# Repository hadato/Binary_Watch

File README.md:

# Binary Watch

This is a project of binary watch which is able to show time, date and its battery level. Three side LEDs show what is currently on display. The watch is based on an ATMega328p and a PCF8563 real-time clock. All control is done using one press bottom. Light-sensing is implemented for brightness adjustments. 

## Description

### Repository and Project Status

The repository contains a first prototype of the watch to be implemented in a wooden hand watch. Both source code, board design files are included. The first prototype has been implemented on a breadboard and is fully functional. The second prototype was build in a wooden wrist watch and is fully functional.

### Main Watch Components
- 25 LEDs
- ATMega328p microcontroller
- PCF8563 real-time clock
- Small tactile switch
- MCP73831T Li-Ion battery charger
- Rechargeable 2032 Li-Ion battery
- Phototransistor for LED intensity adjustment
- USB connector for charging

### Working Principle

The main part of the project is based on an 8-bit microcontroller (uC) ATMega328p connected to the PCF8563 real-time clock (RTC) using I2C. The RTC keeps the correct time, whereas the uC is responsible for all logical operations, inputs from the button and LED output. When the button is pressed, the uC wakes up and the current time is read from the RTC. The time (hours, minutes, seconds) is displayed in a binary-coded decimal (BCD) format on the LEDs using multiplexing. If the button is pressed shortly once more, date (day, month, year) is displayed. Third short press shows the battery voltage. Another short press puts the uC to the sleep mode again. If the button is not pressed for more than 8 s, the uC goes to the sleep mode and all LED are turned off. If a longer press is performed, the watch goes into the sleep mode from either of the previous states. 

To enter the time-setting mode, the button has to be pressed for more than 1 s in either of the previously mentioned modes. If the time-setting mode is entered, a variable to be set starts to blink (first, variable second starts to blink). A short press increments the corresponding variable, longer press (over 0.25s) moves to the next variable (seconds -> minutes -> hours -> day -> month -> year), extra long press confirms the changes and makes the watch to return to the time-display mode.

To save the energy during the run-time and minimize the parts-count, the uC runs on an internal 1 MHz oscillator.

### Code

Note: As included, the code is working though it is still under development and far from being optimal.

The watch is programmed in C++ and is split into three different parts. For the communication with the RTC, twi.h and twi.cpp files were created. For the basic watch operation (button press, LED multiplexing, time reading/setting) a watch.h and watch.cpp files were created. The main.cpp then binds everything together. 

### Board Design

The board is designe using EAGLE and its lates version (9.5.1). The file Top_final shows a look of the watch, the files Top_copper and Bot_copper show the board design. Files BinaryWatch_v0_4_OptR_fix are the EAGLE files.

## Future Goals

- Improve the coding and commenting
- Making a more versatile design which can be used in different watches ranging from tiny hand watches to table/wall watches.
- Implement USB communication with PC to be able to conveniently set up time on the watch (different uC needed).

## Other Pictures

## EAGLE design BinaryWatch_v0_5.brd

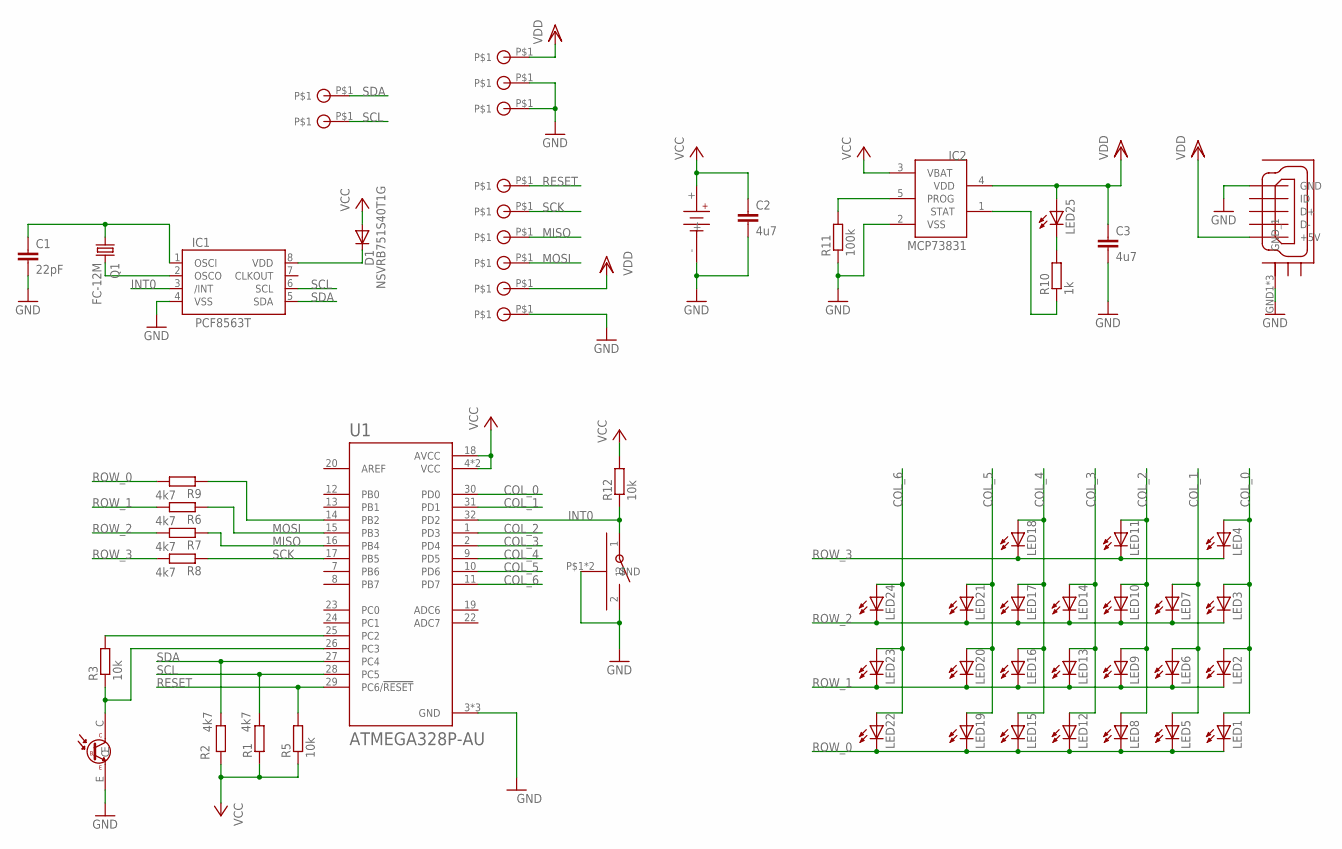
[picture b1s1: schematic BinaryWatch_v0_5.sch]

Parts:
C1: 22pF; C0603
C2, C3: 4u7; C0603
D1: NSVRB751S40T1G; SOD523
IC1: PCF8563T; SO8
IC2: MCP73831; SOT23-5L
LED1, LED2, LED3, LED4, LED5, LED6, LED7, LED8, LED9, LED10, LED11, LED12, LED13, LED14, LED15, LED16, LED17, LED18, LED19, LED20, LED21, LED22, LED23, LED24, LED25: LEDSML0603; SML0603
Q1: FC-12M
R1, R2, R6, R7, R8, R9: 4k7; R0603
R3, R5, R12: 10k; R0603
R10: 1k; R0603
R11: 100k; R0603
U1: ATMEGA328P-AU; QFP80P900X900X120-32N
U$1: 2032; 2032_45DEG
U$2, U$3, U$4, U$5, U$6, U$7, U$9, U$11, U$12, U$13, U$14: CONTACT_1_8MM
U$8: TACK_SWITCH; TL3330
U$10: MICRO_USB_VERTICAL
U$15: PHOTOTRANSISTOR_0603; PHOTO_TRANS_0603

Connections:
COL_0: LED1.A, LED2.A, LED3.A, LED4.A, U1.30 (PD0)
COL_1: LED5.A, LED6.A, LED7.A, U1.31 (PD1)
COL_2: LED8.A, LED9.A, LED10.A, LED11.A, U1.1 (PD3)
COL_3: LED12.A, LED13.A, LED14.A, U1.2 (PD4)
COL_4: LED15.A, LED16.A, LED17.A, LED18.A, U1.9 (PD5)
COL_5: LED19.A, LED20.A, LED21.A, U1.10 (PD6)
COL_6: LED22.A, LED23.A, LED24.A, U1.11 (PD7)
GND: C1.2, C2.2, C3.2, IC1.4 (VSS), IC2.2 (VSS), R11.1, U1.3 (GND), U1.5 (GND), U1.21 (GND), U$1.-, U$2.P$1, U$8.2, U$8.P$1 (GND), U$8.P$2 (GND), U$9.P$1, U$10.5 (GND), U$10.GND1 (GND_1), U$10.GND2 (GND_1), U$10.GND3 (GND_1), U$12.P$1, U$15.E
INT0: IC1.3 (/INT), R12.1, U1.32 (PD2), U$8.1
MISO: R7.1, U1.16 (PB4), U$5.P$1
MOSI: R6.1, U1.15 (PB3), U$4.P$1
unnamed: IC1.2 (OSCO), Q1.2
unnamed: C1.1, IC1.1 (OSCI), Q1.1
unnamed: R3.1, U1.26 (PC3), U$15.C
unnamed: R3.2, U1.25 (PC2)
unnamed: R9.1, U1.14 (PB2)
unnamed: D1.C, IC1.8 (VDD)
unnamed: IC2.1 (STAT), R10.1
unnamed: LED25.C, R10.2
unnamed: IC2.5 (PROG), R11.2
RESET: R5.2, U1.29 (PC6/!RESET), U$7.P$1
ROW_0: LED1.C, LED5.C, LED8.C, LED12.C, LED15.C, LED19.C, LED22.C, R9.2
ROW_1: LED2.C, LED6.C, LED9.C, LED13.C, LED16.C, LED20.C, LED23.C, R6.2
ROW_2: LED3.C, LED7.C, LED10.C, LED14.C, LED17.C, LED21.C, LED24.C, R7.2
ROW_3: LED4.C, LED11.C, LED18.C, R8.2
SCK: R8.1, U1.17 (PB5), U$6.P$1
SCL: IC1.6 (SCL), R1.2, U1.28 (PC5), U$14.P$1
SDA: IC1.5 (SDA), R2.2, U1.27 (PC4), U$13.P$1
VCC: C2.1, D1.A, IC2.3 (VBAT), R1.1, R2.1, R5.1, R12.2, U1.4 (VCC), U1.6 (VCC), U1.18 (AVCC), U$1.+
VDD: C3.1, IC2.4 (VDD), LED25.A, U$3.P$1, U$10.1 (+5V), U$11.P$1

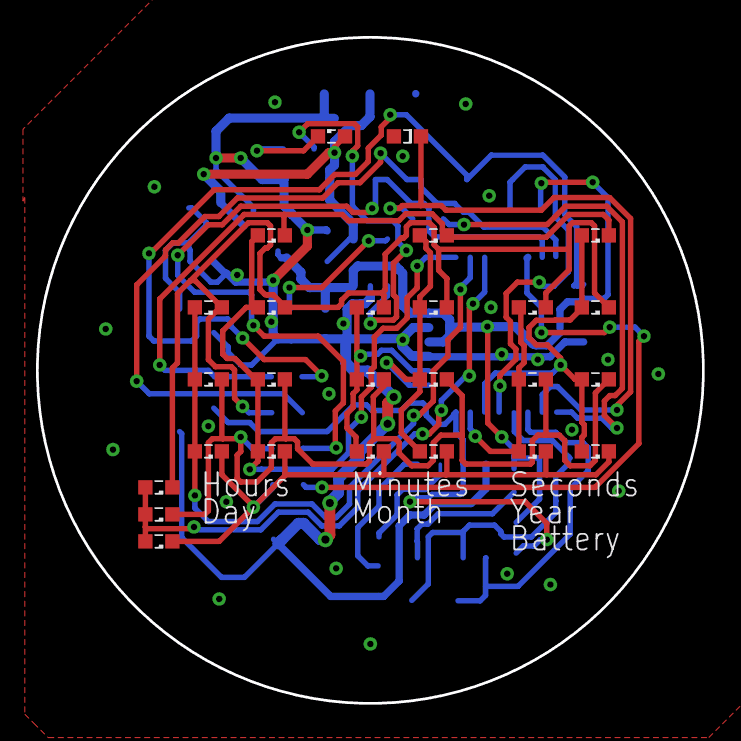
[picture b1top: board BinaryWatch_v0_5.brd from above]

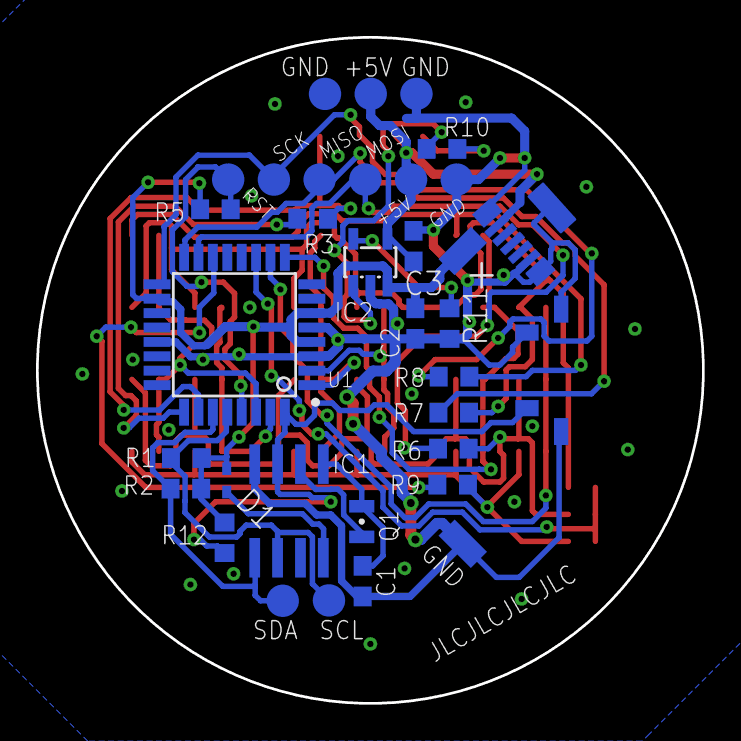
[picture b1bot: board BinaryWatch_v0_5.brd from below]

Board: 2 copper layers, 37.0 x 37.0 mm, 59 parts (33 on the bottom side), 30 nets.

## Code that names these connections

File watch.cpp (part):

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	ADC_timer0_init();						//Initialize timer0 for the delayed measurements of power supply voltage
	
	//ADC
	DDRC  |= (1 << PC2);	// set PC2 as output
	PORTC |= (1 << PC2);	// set PC2 high - turn the power up for the photo-resistor
}

void watch::ADC_enable(){
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
void watch::ADC_disable(){
	ADCSRA &= ~(1 << ADEN);	//Disable ADC
	DDRC   |= (1 << PC3);	//Set PC3 as output
	PORTC  &= ~(1 << PC3);	//Set PC3 low
	PORTC  &= ~(1 << PC2);	//Set PC2 low
}

void watch::ADC_start(){
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	ADC_enable();
	ADMUX = ADMUX_ADC_LIGHT;		// set to measure the voltage on the opto-resistor
	ADC_stat = MEASURE_LIGHT;		// set the ADC status: measure the opto-resistor
	DDRC  &= ~(1 << PC3);			// set PC3 as input - for the opto-resistor measurement
	PORTC |= (1 << PC2);			// set the supply pin PC2 high - turn the power to the opto-resistor
	for (int i = 0; i < 10; i++);	// wait for a bit to get the voltage settle 
	ADC_start();
	return 0;
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
void watch::button_init(){
	//Button press
	DDRD  &= ~(1 << PD2);   // set PD2 (PCINT0) to input
	//PORTD |= (1 << PD2);    // turn On the Pull-up
	PORTD &= ~(1 << PD2);	// Turn Off the Pull-up
	EIMSK |= (1 << INT0);     // Turns on INT0 in a normal operation mode (active low)
}

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
	//cli();					//disable all interrupts
	
	DDRB |= 0b00111100;		//set PB2-PB5 as outputs
	DDRD |= 0b11111011;		//set PD0, PD1, PD3-PD7 as outputs
	
	//Turn of not used modules
	PRR |= (1 << PRUSART0);		// Turn off the USART0
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
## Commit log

2019-11-11 Repo created on GitHub
    Final prototype version of the watch
2019-11-11 Created README.md file
2019-11-11 Updated README.md with Board Design
2019-11-11 Updated README.md - Picture preview added
2019-11-12 Added pictures of the Top and Bot copper design
2019-11-29 Updated pictures
    Eagle pictures update and read product picture added
2019-11-29 Old Bot_Copper removed
2019-11-29 Deleted big size picture
2019-11-29 Added final version of the prototype
2019-11-29 Updated README with prototype picture
    A wooden hand watch prototype has been added
2019-11-29 Added new board files
2019-11-29 Deleting old bord files
2019-11-29 Deleting old schematic
2020-01-14 Added new pictures
2020-01-14 Revised code
